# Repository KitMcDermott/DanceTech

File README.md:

# V2 of Dance Tech - Last edit December 2021

Creative computing kits for dancers and cheerleaders

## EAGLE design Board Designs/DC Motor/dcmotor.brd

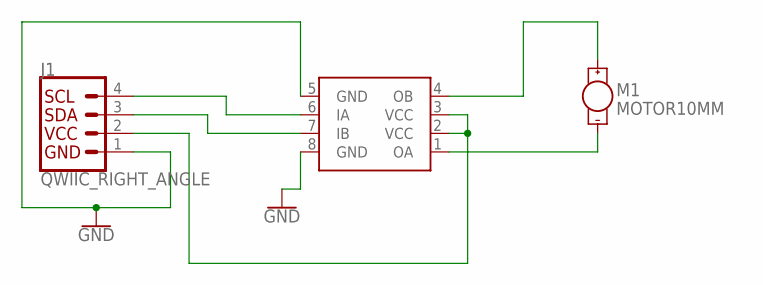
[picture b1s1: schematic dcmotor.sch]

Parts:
J1: QWIIC_RIGHT_ANGLE; JST04_1MM_RA
M1: MOTOR10MM; VIBE-MOTOR-10MM
U$1: L9110SO8; SO-08

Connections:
GND: J1.1, U$1.5 (GND), U$1.8 (GND)
unnamed: M1.+, U$1.4 (OB)
unnamed: M1.-, U$1.1 (OA)
unnamed: J1.4, U$1.6 (IA)
unnamed: J1.3, U$1.7 (IB)
unnamed: J1.2, U$1.2 (VCC), U$1.3 (VCC)

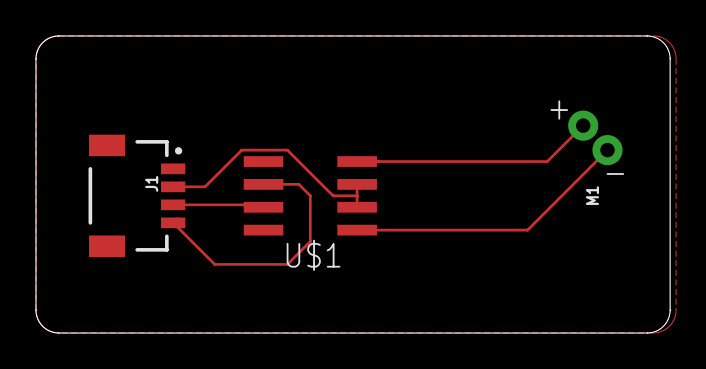
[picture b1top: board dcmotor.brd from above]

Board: 2 copper layers, 35.2 x 16.5 mm, 3 parts (0 on the bottom side), 6 nets.

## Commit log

2022-12-02 Create Version1
2022-12-02 Delete Accessory Design Files directory
    reuploading everything in one folder to organize version 1
2022-12-02 Version 1 Files zipped
    Version 1 2020

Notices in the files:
parts and their libraries:
SparkFun-Connectors: Licensing: Creative Commons ShareAlike 4.0 International - https://creativecommons.org/licenses/by-sa/4.0
